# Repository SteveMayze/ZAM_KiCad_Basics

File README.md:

# Introduction to KiCad
## Workshop proposal for ZAM

# OVERVIEW & PURPOSE
The creation of projects in electronics requires the connection of various components to build a circuit. There are various means to achieve this - breadboard, verro-board. However there are many advantages to building an own Printed Circuit Board (PCB). The purpose of this workshop is to introduce the attendees to the KiCad electronic design tool so that they will gain the know-how and confidence to create their own PCBs. This will not be a class in electronics. Knowledge in electronics would be an advantage but not a requirement.

# AUDIENCE
The intended audience are complete newcomers to KiCad. Even to electronics. Current users of KiCad may not gain any further insight into the application or features. Advanced topics like RF interference mitigation will not be covered.
The maximum number of attendees should be limited to 10 in conjunction with the latest ZAM infection protection concepts.
# TIMING
The main part of the workshop would be planned to take place on one day. Two further follow-up workshops could be offered to complete the attendees projects.  The sessions should be as interactive as possible where every 45 minute session is limited to a 20 minute explanation. The remaining 25 minutes is then for attendee practice and questions.
No timing has been allocated for software installation. This would affect the overall time, but it can not be assumed that all attendees will come with KiCad already installed, nor can it be guaranteed that all attendees will have a laptop.

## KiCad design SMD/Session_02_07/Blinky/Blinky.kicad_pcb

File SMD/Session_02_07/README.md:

# ZAM KiCad Basics

## 2.7 Sending off for fabrication.

This can be some on-line service or this can be done in-house with the appropriate etching equipment.

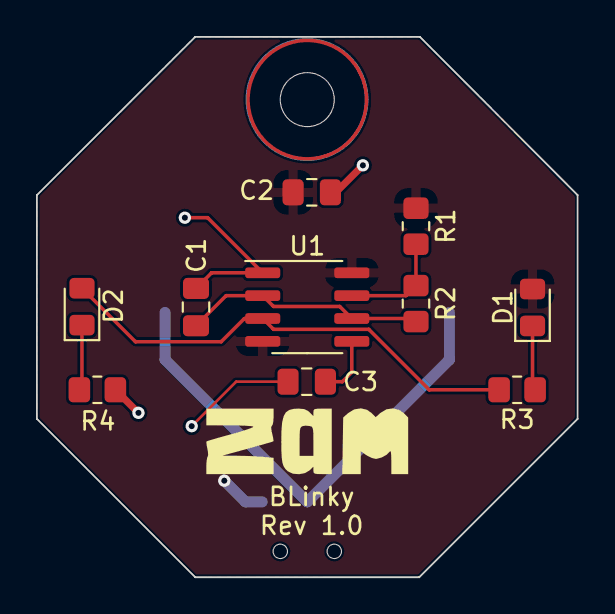
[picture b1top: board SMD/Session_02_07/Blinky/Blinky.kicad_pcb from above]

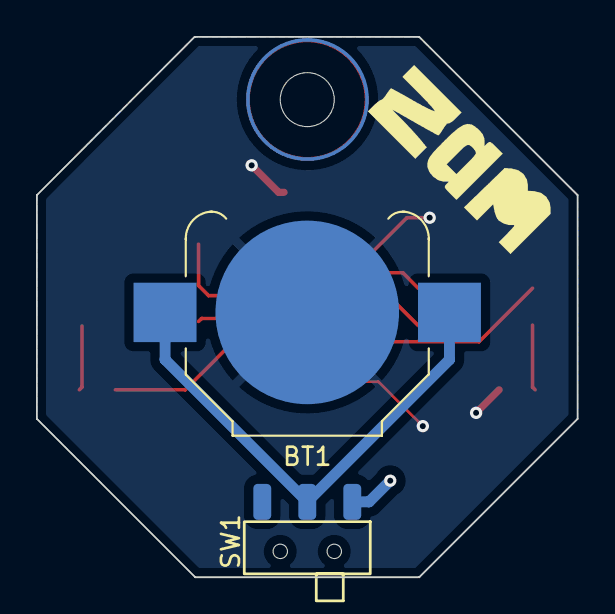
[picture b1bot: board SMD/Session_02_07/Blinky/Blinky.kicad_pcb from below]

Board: 2 copper layers, 30.0 x 30.0 mm, 15 parts (3 on the bottom side), 9 nets.

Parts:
BT1: Battery_Cell; BatteryHolder_Keystone_3000_1x12mm
C1: 300nF; C_0805_2012Metric_Pad1.18x1.45mm_HandSolder
C2, C3: 100nF; C_0805_2012Metric_Pad1.18x1.45mm_HandSolder
D1, D2: LED; LED_0805_2012Metric_Pad1.15x1.40mm_HandSolder
H?: MountingHole; MountingHole_3mm
LG2: LOGO; ZAM_LOGO_440
LG?: LOGO; ZAM_LOGO_440
R1: 10kΩ; R_0805_2012Metric_Pad1.20x1.40mm_HandSolder
R2: 1MΩ; R_0805_2012Metric_Pad1.20x1.40mm_HandSolder
R3, R4: 200Ω; R_0805_2012Metric_Pad1.20x1.40mm_HandSolder
SW?: SW_SPDT; SSK-1202
U1: TLC551CD‎; SOIC-8_3.9x4.9mm_P1.27mm

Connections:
/VCC: C2.1, D1.2 (A), R1.1, SW?.1 (A), U1.4 (RESET), U1.8 (Vdd)
GND: BT1.2 (-), C1.2, C2.2, C3.2, R4.2, U1.1 (GND)
unnamed: BT1.1 (+), SW?.2 (B)
unnamed: C1.1, R2.2, U1.2 (TR), U1.6 (THR)
unnamed: C3.1, U1.5 (CNT)
unnamed: D1.1 (K), R3.1
unnamed: D2.1 (K), R4.1
unnamed: D2.2 (A), R3.2, U1.3 (OUT)
unnamed: R1.2, R2.1, U1.7 (DIS)

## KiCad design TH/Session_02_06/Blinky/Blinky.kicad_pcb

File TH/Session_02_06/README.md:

# ZAM KiCad Basics

# Session 2.6 Finishing up and preparing for Fabrication
Checking the Gerber files.

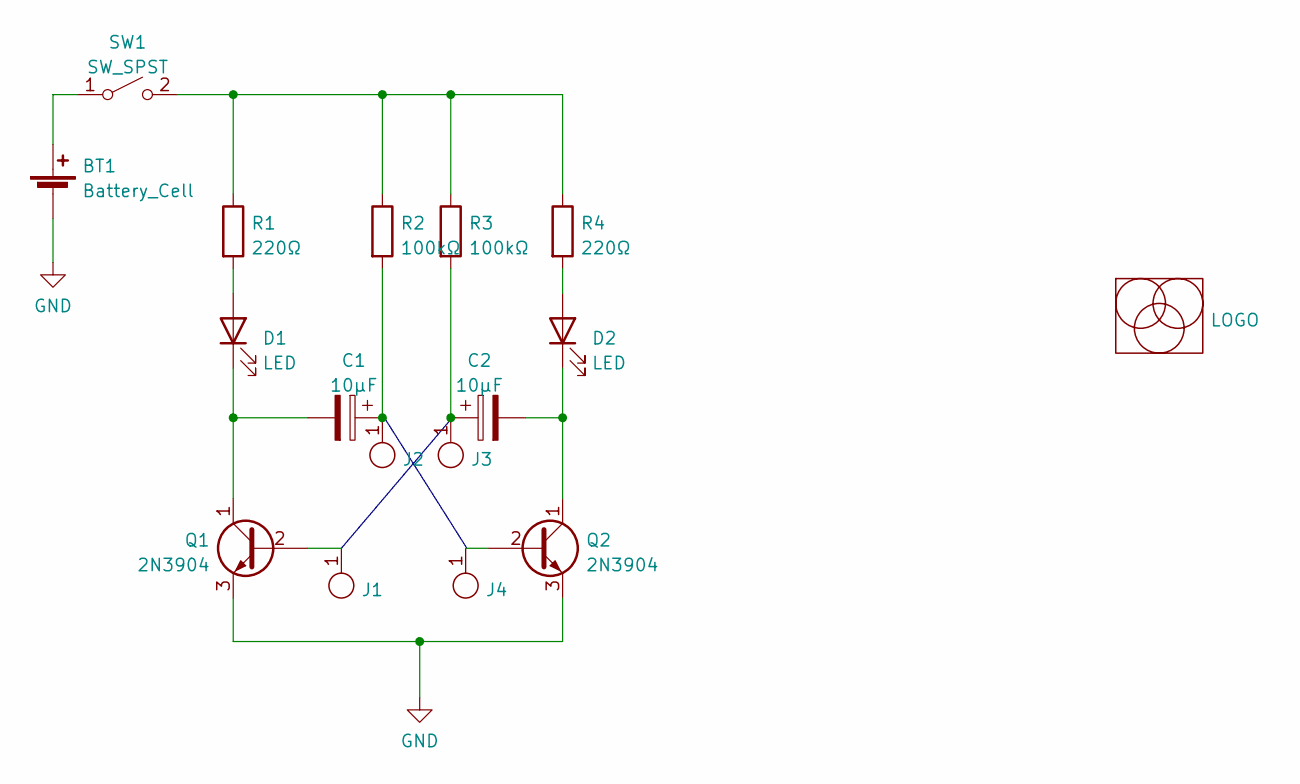
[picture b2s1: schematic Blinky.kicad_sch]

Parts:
BT1: Battery_Cell; BatteryHolder_Keystone_3000_1x12mm
C1, C2: 10μF; CP_Radial_D5.0mm_P2.50mm
D1, D2: LED; LED_D5.0mm
J1, J2, J4: bridge; TestPoint_THTPad_2.0x2.0mm_Drill1.0mm
J3: Jumper_1; TestPoint_THTPad_2.0x2.0mm_Drill1.0mm
LG2: LOGO; ZAM_LOGO_440_stopMask
Q1, Q2: 2N3904; TO-92_Inline
R1, R4: 220Ω; R_Axial_DIN0207_L6.3mm_D2.5mm_P2.54mm_Vertical
R2, R3: 100kΩ; R_Axial_DIN0207_L6.3mm_D2.5mm_P2.54mm_Vertical
SW1: SW_SPST; SSK-1202

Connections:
GND: BT1.2 (-), Q1.3 (E), Q2.3 (E)
unnamed: BT1.1 (+), SW1.1 (A)
unnamed: C1.1, J2.1, R2.2
unnamed: C1.2, D1.1 (K), Q1.1 (C)
unnamed 4: C2.1, J3.1, R3.2; also elsewhere on the board
unnamed: C2.2, D2.1 (K), Q2.1 (C)
unnamed: D1.2 (A), R1.2
unnamed: D2.2 (A), R4.2
unnamed: J1.1, Q1.2 (B)
unnamed: J4.1, Q2.2 (B)
unnamed: R1.1, R2.1, R3.1, R4.1, SW1.2 (B)

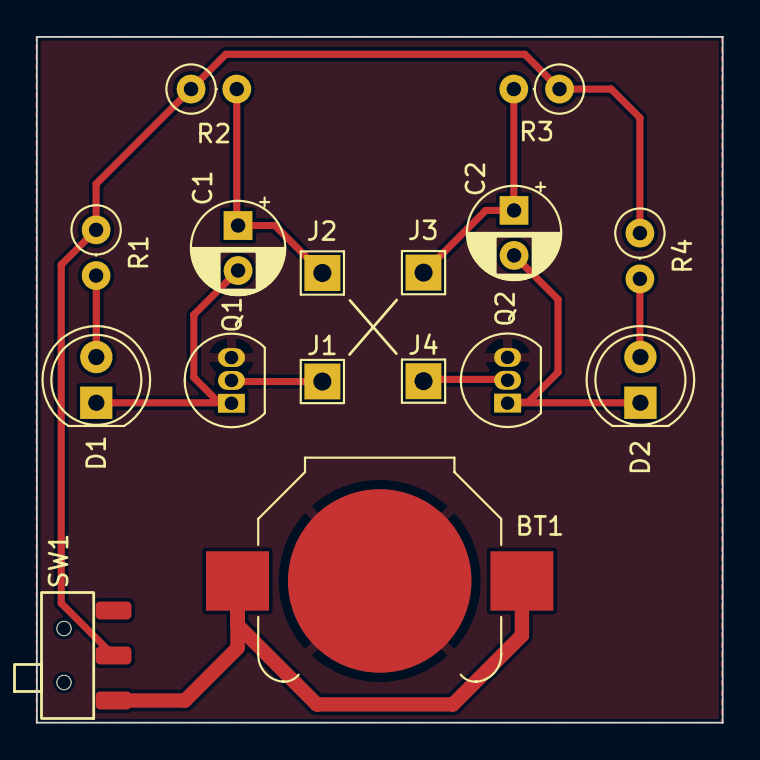
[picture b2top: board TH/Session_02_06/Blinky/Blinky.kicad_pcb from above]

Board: 2 copper layers, 38.1 x 38.1 mm, 17 parts (0 on the bottom side), 11 nets.

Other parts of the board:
J?: Jumper_1; TestPoint_THTPad_2.0x2.0mm_Drill1.0mm

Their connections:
unnamed 4: J?.1; also elsewhere on the board

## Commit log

2022-03-18 Adding some modules
2022-03-26 Adding some chapters
2022-04-03 Finished the first draft of the work steps
2022-04-03 Created a Throughole version of the design files
2022-04-07 Revamps the through-hole project as transistor based
2022-04-09 Makes corrections to the design rules
2022-04-12 For the BOM
2022-04-12 Corrections to the switch footprint
2022-04-21 Correction to the NPN symbol to the purchased part Session_02_06 only
2022-05-10 Adds the BOM
2022-06-03 Collecting useful files together
